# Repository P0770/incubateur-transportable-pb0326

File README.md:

# PB-0326 — Incubateur transportable pour cellules

Boîtier autonome qui transporte des cellules vivantes pendant une heure de train entre Lausanne et Genève, en maintenant **37 °C**, une humidité proche de **100 %** et un **pH de 7,2 à 7,4** grâce à l'injection de CO₂.

Projet Thématique 2026 — HEPIA (HES-SO Genève), Bachelor en ingénierie microtechnique, spécialisation biomédicale.
**Auteurs : Lyla Founas et Mattéo Pozzo di Borgo.**

---

## Le problème

Les cellules mammifères ne survivent qu'à 37 °C, dans une atmosphère saturée en humidité (sinon le milieu s'évapore et devient cytotoxique) et à un pH de 7,2 à 7,4, régulé par le CO₂ dissous. Les solutions commerciales (Cellbox Go, Phoenix…) sont conçues pour des trajets de 12 à 72 h : lourdes et coûteuses pour un trajet d'une heure. D'où ce prototype sur mesure.

**Cahier des charges**

| Critère | Valeur cible |
|---|---|
| Autonomie | ≥ 1 h sans prise secteur |
| Poids / format | < 10 kg, valise cabine 45 × 36 × 20 cm |
| Température zone biologique | 37,0 °C ± 0,5 °C |
| Humidité relative | ≈ 100 % |
| pH du milieu (via CO₂) | 7,2 – 7,4 |
| Préparation | < 5 min, sans formation technique |

## Architecture

Un **boîtier biologique amovible** (tupperware équipé) se dépose dans la valise ; des **connecteurs aimantés** établissent d'un seul geste l'alimentation, les capteurs et la chauffe (système « pick and place »).

| Fonction | Solution retenue |
|---|---|
| Chauffage | Résistance bobinée 8,2 Ω (50 W nominaux, ≈ 17,6 W sous 12 V), MOSFET IRLZ44N |
| Humidification | Éponge cellulose passive |
| Régulation du pH | Injection de CO₂ : réservoir → détendeur → électrovanne → zone biologique |
| Mesure T / HR | Sensirion SHT35 (I²C) dans la zone biologique |
| Mesure CO₂ | Sensirion SCD40 (I²C), protégé de l'humidité par une membrane Nafion |
| Brassage | Ventilateur 5 V sur MOSFET |
| Contrôle | ESP32-DevKitC |
| Interface | Écran ST7789 240 × 280, LED rouge d'alerte, LED I²C, buzzer, bouton GO |
| Alimentation | 2 × LiPo 3S 5000 mAh + BMS, DC-DC 12 V (puissance) et 5 V (logique) |

Schéma électronique complet : [`electronique/schema_electronique.pdf`](electronique/schema_electronique.pdf)

## Firmware

Le firmware ([`firmware/firmware_PB0326/firmware_PB0326.ino`](firmware/firmware_PB0326/firmware_PB0326.ino)) est organisé autour d'une machine à états finis, pilotée par un seul bouton **GO** :

L'**historique Git** de ce dépôt retrace l'évolution réelle du code, de la v2.0 (22 mai 2026) à la v4.0.1 (juin 2026), où le module Peltier a été remplacé par la résistance chauffante.

### Compiler et téléverser

1. **Arduino IDE** avec le paquet de cartes **esp32** (Espressif), carte **ESP32 Dev Module**.
2. Bibliothèques (gestionnaire de bibliothèques) :
   - `TFT_eSPI` (Bodmer)
   - `Adafruit SHT31 Library` (Adafruit)
3. Configurer l'écran : remplacer `User_Setup.h` dans le dossier de la bibliothèque TFT_eSPI par [`firmware/User_Setup.h`](firmware/User_Setup.h).
   ⚠️ Ce fichier a été reconstitué d'après les commentaires du code : à vérifier au premier essai.
4. Ouvrir `firmware/firmware_PB0326/firmware_PB0326.ino` et téléverser.
5. Moniteur série à **115 200 bauds** : les mesures T et HR s'affichent toutes les 2 s.

### Brochage

| Signal | GPIO |
|---|---|
| Résistance chauffante (MOSFET) | 32 |
| Ventilateur (MOSFET) | 14 |
| Électrovanne CO₂ (MOSFET) | 27 |
| LED rouge (erreur) | 19 |
| LED I²C (capteur détecté) | 4 |
| Bouton GO | 5 |
| Buzzer | 25 |
| I²C — SDA / SCL | 21 / 22 |
| Écran SPI — MOSI / SCLK / CS / DC / RST | 23 / 18 / 15 / 2 / 33 |

## Résultats

Les essais ont été menés avec la boîte de culture vide : l'affichage, la régulation de la température, de l'humidité et du CO₂ ainsi que les sécurités (passage en ERREUR, coupure des actionneurs, alerte) fonctionnent comme prévu.

La tenue des paramètres sur une heure complète n'a **pas encore été enregistrée**. En attendant, une **simulation numérique** du comportement attendu, fondée sur la loi de commande réelle du firmware, est disponible dans [`docs/simulation/`](docs/simulation/) (script Python reproductible) :

## Contenu du dépôt

```
firmware/        Code ESP32 (Arduino) + configuration de l'écran
electronique/    Schéma (PDF + images), projets KiCad, carte support SHT3x avec fichiers Gerber
mecanique/
  cao/           Fichiers Creo (versions finales) et Inventor
  impression-3d/ Fichiers STL et 3MF des pièces imprimées
  rendus/        Rendus CAO
docs/            Présentation, planning, rapport intermédiaire, diagrammes, simulation
media/           Photos et vidéo du prototype
```

## Documents

- [`docs/presentation_PB0326.pdf`](docs/presentation_PB0326.pdf) — **présentation finale (juin 2026), document de référence** pour les choix du prototype.
- [`docs/rapport_intermediaire_catalogue_idees.pdf`](docs/rapport_intermediaire_catalogue_idees.pdf) — catalogue d'idées et analyse des solutions, rédigé pendant la **phase d'exploration**. Certains choix y diffèrent du prototype final (module Peltier, tampon HEPES, sonde pH) : ils ont été revus ensuite, voir la présentation.
- [`docs/gantt_PB0326.pdf`](docs/gantt_PB0326.pdf) — planning du projet.

## Modèles tiers non inclus

Pour des raisons de licence, les modèles CAO fournis par des fabricants ne sont pas redistribués ici. Certains assemblages peuvent donc signaler des références manquantes :

- valise Pelican 1450 ;
- capteur Sensirion SCD40 ;
- pogo pins Attend 303C-321018-30-04 ;
- bibliothèque de symbole ESP32-DevKitC-32U (KiCad).

Ils sont téléchargeables gratuitement sur les sites des fabricants.

## Pistes d'amélioration

- Suivi à distance par Wi-Fi (application mobile) avec alerte pendant le trajet
- Régulation PID de la température pour réduire les oscillations
- Enregistrement des paramètres sur toute la durée du transport
- Module Peltier pour pouvoir aussi refroidir
- Humidification par injection de vapeur

## Licence

- Code (`firmware/`, `docs/simulation/`) : **MIT**
- Conception, documents et images : **CC BY-NC-SA 4.0**

Voir [`LICENSE`](LICENSE) et [`LICENSE-CC-BY-NC-SA-4.0.md`](LICENSE-CC-BY-NC-SA-4.0.md).

---

Portfolio de Mattéo Pozzo di Borgo : [p0770.github.io](https://p0770.github.io/projects/incubateur-cellules)

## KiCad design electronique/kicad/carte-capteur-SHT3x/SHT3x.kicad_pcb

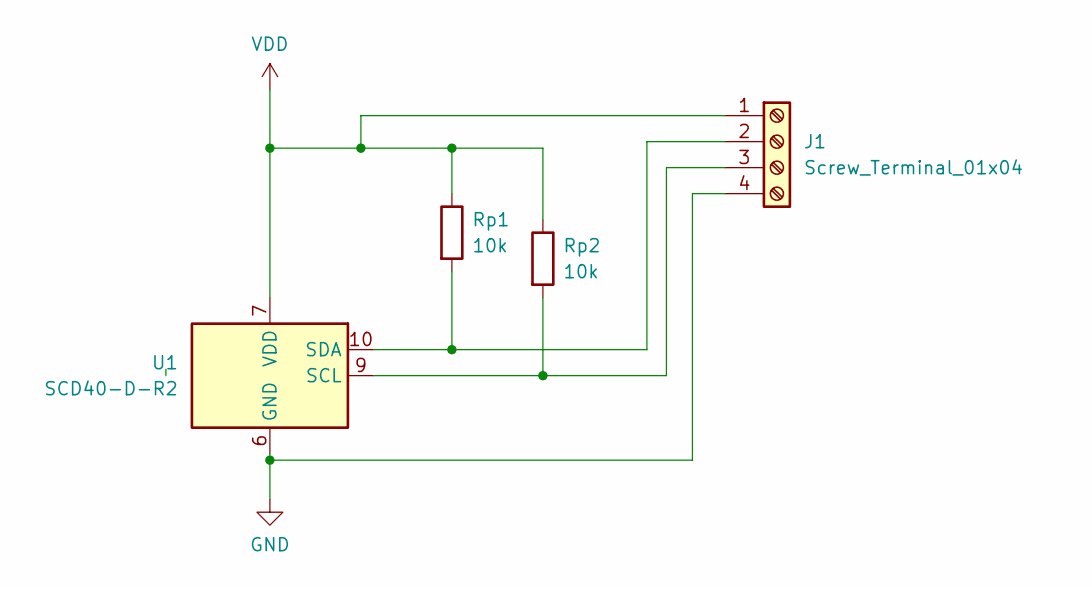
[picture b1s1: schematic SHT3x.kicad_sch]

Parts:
J1: Screw_Terminal_01x04; TerminalBlock_Altech_AK300-4_P5.00mm
Rp1, Rp2: 10k; R_Axial_DIN0918_L18.0mm_D9.0mm_P7.62mm_Vertical
U1: SCD40-D-R2; Sensirion_SCD4x-1EP_10.1x10.1mm_P1.25mm_EP4.8x4.8mm

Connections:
GND: J1.4, U1.6 (GND), U1.20 (GND), U1.21 (GND)
unnamed: J1.2, Rp1.2, U1.10 (SDA)
unnamed: J1.3, Rp2.2, U1.9 (SCL)
VDD: J1.1, Rp1.1, Rp2.1, U1.7 (VDD), U1.19 (VDD)

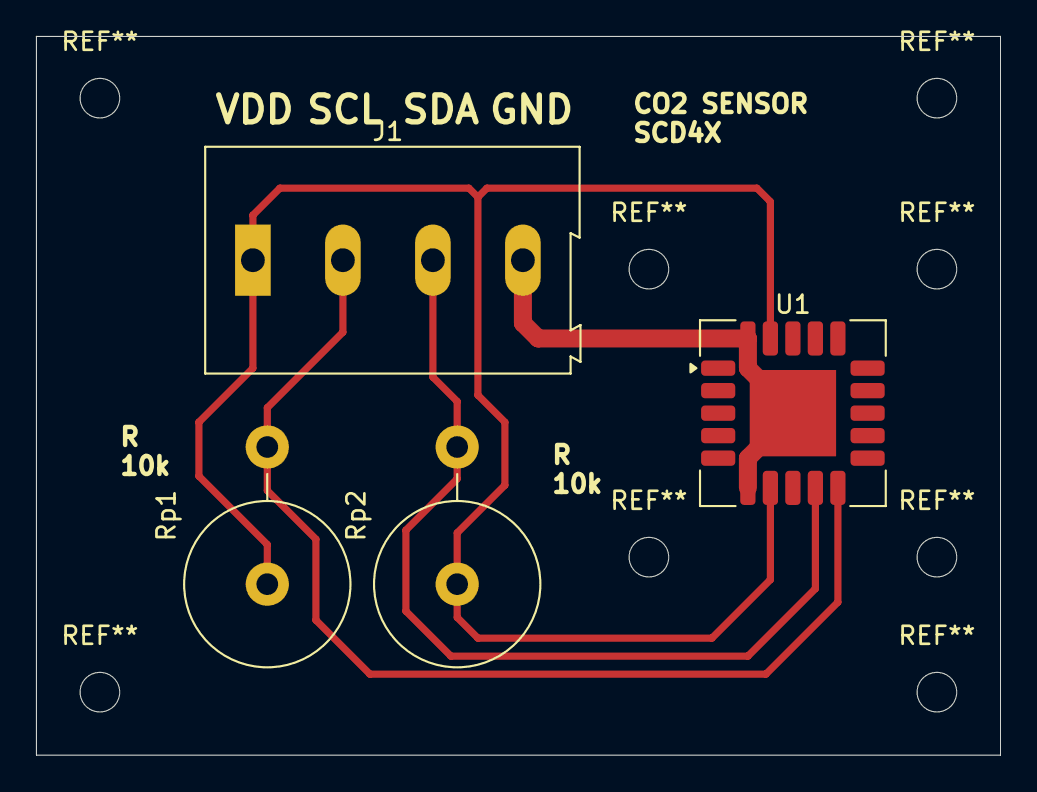
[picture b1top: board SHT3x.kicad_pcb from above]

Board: 2 copper layers, 53.6 x 39.9 mm, 4 parts (0 on the bottom side), 4 nets.
